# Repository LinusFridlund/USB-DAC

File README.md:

# USB-DAC
A high quality USB audio DAC.
This project is intended as a test for my larger music streamer project that implements a DAC chip together with a STM32 microconroller.
It accepts a music stream over USB, outputs the analog audio over balanced XLR connections and has an OLED display to show stream info. 

Image of a render of the PCBs together with  the case.

## Hardware
The main part of the hardware is the custom developed PCB housing the STM32, DAC chip and its accompanying components

### Microcontroller
A STM32H7 series microcontroller was chosen for its high performance and support for interfaces such as USB HS and SAI (Serial Audio Interface) which are used in the project. In addition I also have previous experience with STM32 based systems. Cost and power consumption were no priorities here since I am only building one unit and it is powered by an external power supply.

### DAC Chip
The DAC chip used is the ESS ES9039Q2M. It is a chip that is widely used in many other DACs meaning other designs are easy to reference. The datasheet includes important info about recommended output stages, power supply schemes and all the neccesary software details. For these reasons, along with its availability online made it a good choice.

### Power supply
A small PSU board with a Mean Well 12V supply feeds into a +-12V switching power supply on the main DAC board. The outptus then get filtered through a ferrite bead and a pi filter before being regulated to +-9V and 3.3V for the analog section. The incoming 12V also gets regulated down with less filtering to 5 and 3.3V for the digital components.

### PCB Design considerations
Extra attention had to be given to a couple of key areas in the PCB design in order to achieve a good result.
#### Stackup
A 4 layer stackup is used with the top and bottom being signal layers and the inner layers being ground and power in order to provide easy routing and better signal integrity.
#### Digital signal integrity
The USB signals and the ULPI signals between the USB PHY and the STM32 both operate at high frequencies and thus require proper impedance and length matching to ensure their functionality. 
#### 

## Software

The software development will start when the hardware is finished and ordered. So far I have only played around a bit and gotten a rough idea of how it will be structured.

## Current status
Currently the hardware design is finished and the PCBs have arrived. Currently the boards are being assembled, then the software development begins!

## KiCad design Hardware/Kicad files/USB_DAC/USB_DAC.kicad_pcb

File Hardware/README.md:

# Hardware

## PCB

## Enclosure

## Other parts

### Display
The display used is a 2.42 inch 128 x 64 px oled display from waveshare.
Link: https://www.waveshare.com/2.42inch-oled-module.htm

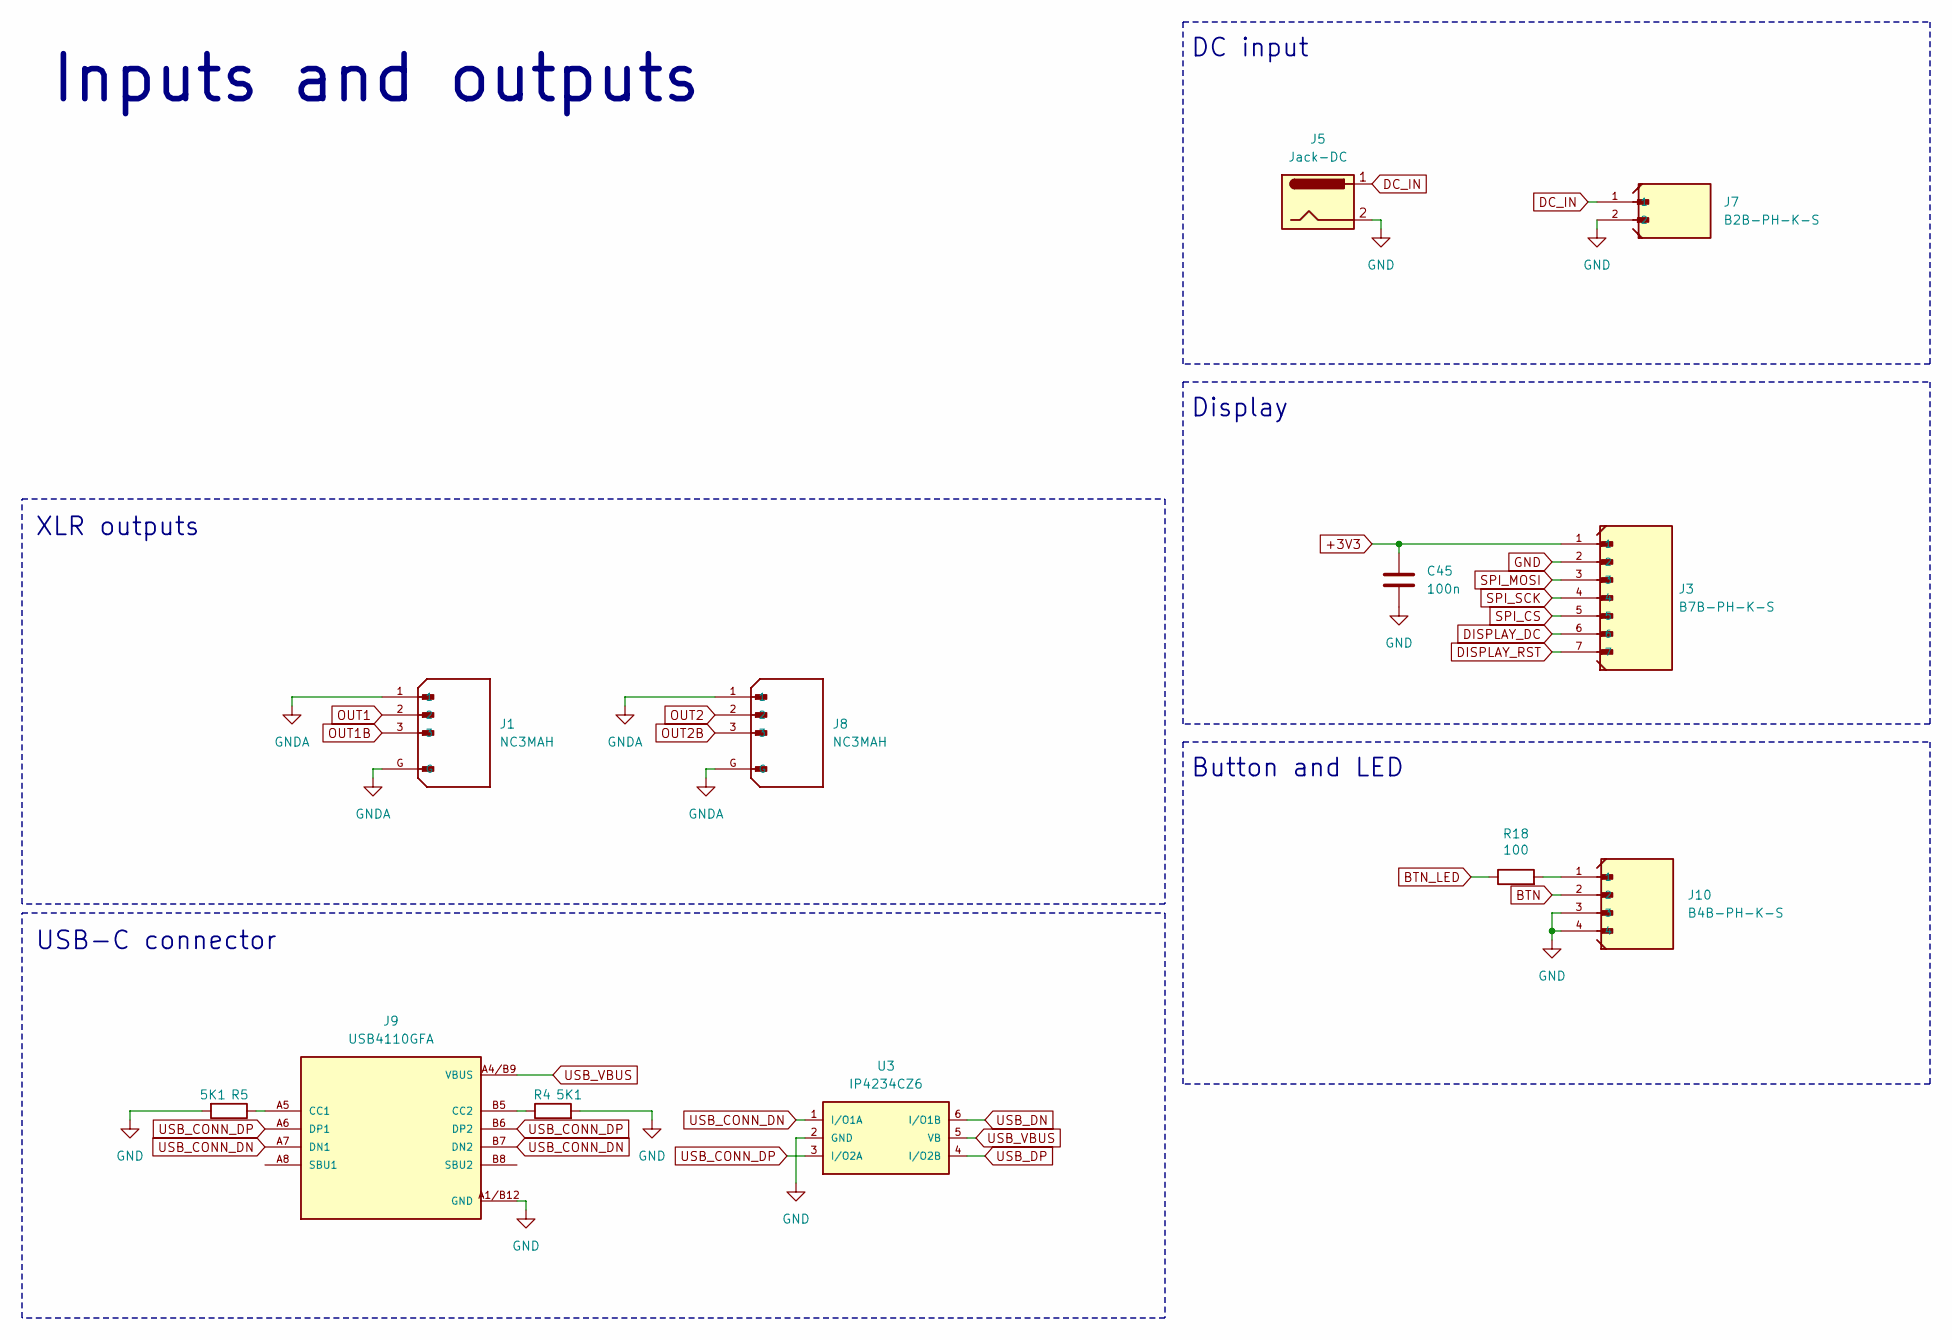
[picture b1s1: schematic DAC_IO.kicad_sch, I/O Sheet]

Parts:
C45: 100n; C_0603_1608Metric
J1, J8: NC3MAH; NEUTRIK_NC3MAH; PARTREV 30.03.09
J3: B7B-PH-K-S; JST_PH_B7B-PH-K_1x07_P2.00mm_Vertical
J5: Jack-DC; BarrelJack_Horizontal
J7: B2B-PH-K-S; JST_B2B-PH-K-S
J9: USB4110GFA; GCT_USB4110GFA
J10: B4B-PH-K-S; JST_B4B-PH-K-S
R4, R5: 5K1; R_0603_1608Metric
R18: 100; R_0603_1608Metric
U3: IP4234CZ6; SOT-457

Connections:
+3V3: C45.1, J3.1; also elsewhere on the board
BTN: J10.2; also elsewhere on the board
BTN_LED: R18.1; also elsewhere on the board
DC_IN: J5.1, J7.1; also elsewhere on the board
DISPLAY_DC: J3.6; also elsewhere on the board
DISPLAY_RST: J3.7; also elsewhere on the board
GNDA: J1.1, J1.G, J8.1, J8.G; also elsewhere on the board
unnamed: J9.A5 (CC1), R5.1
unnamed: J9.B5 (CC2), R4.1
unnamed: J10.1, R18.2
OUT1: J1.2; also elsewhere on the board
OUT1B: J1.3; also elsewhere on the board
OUT2: J8.2; also elsewhere on the board
OUT2B: J8.3; also elsewhere on the board
SPI_CS: J3.5; also elsewhere on the board
SPI_MOSI: J3.3; also elsewhere on the board
SPI_SCK: J3.4; also elsewhere on the board
USB_CONN_DN: J9.A7 (DN1), J9.B7 (DN2), U3.1 (I/O1A)
USB_CONN_DP: J9.A6 (DP1), J9.B6 (DP2), U3.3 (I/O2A)
USB_DN: U3.6 (I/O1B); also elsewhere on the board
USB_DP: U3.4 (I/O2B); also elsewhere on the board
USB_VBUS: J9.A4/B9 (VBUS), J9.B4/A9 (VBUS), U3.5 (VB); also elsewhere on the board

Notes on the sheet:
Button and LED
XLR outputs
Inputs and outputs
Display
DC input
USB-C connector

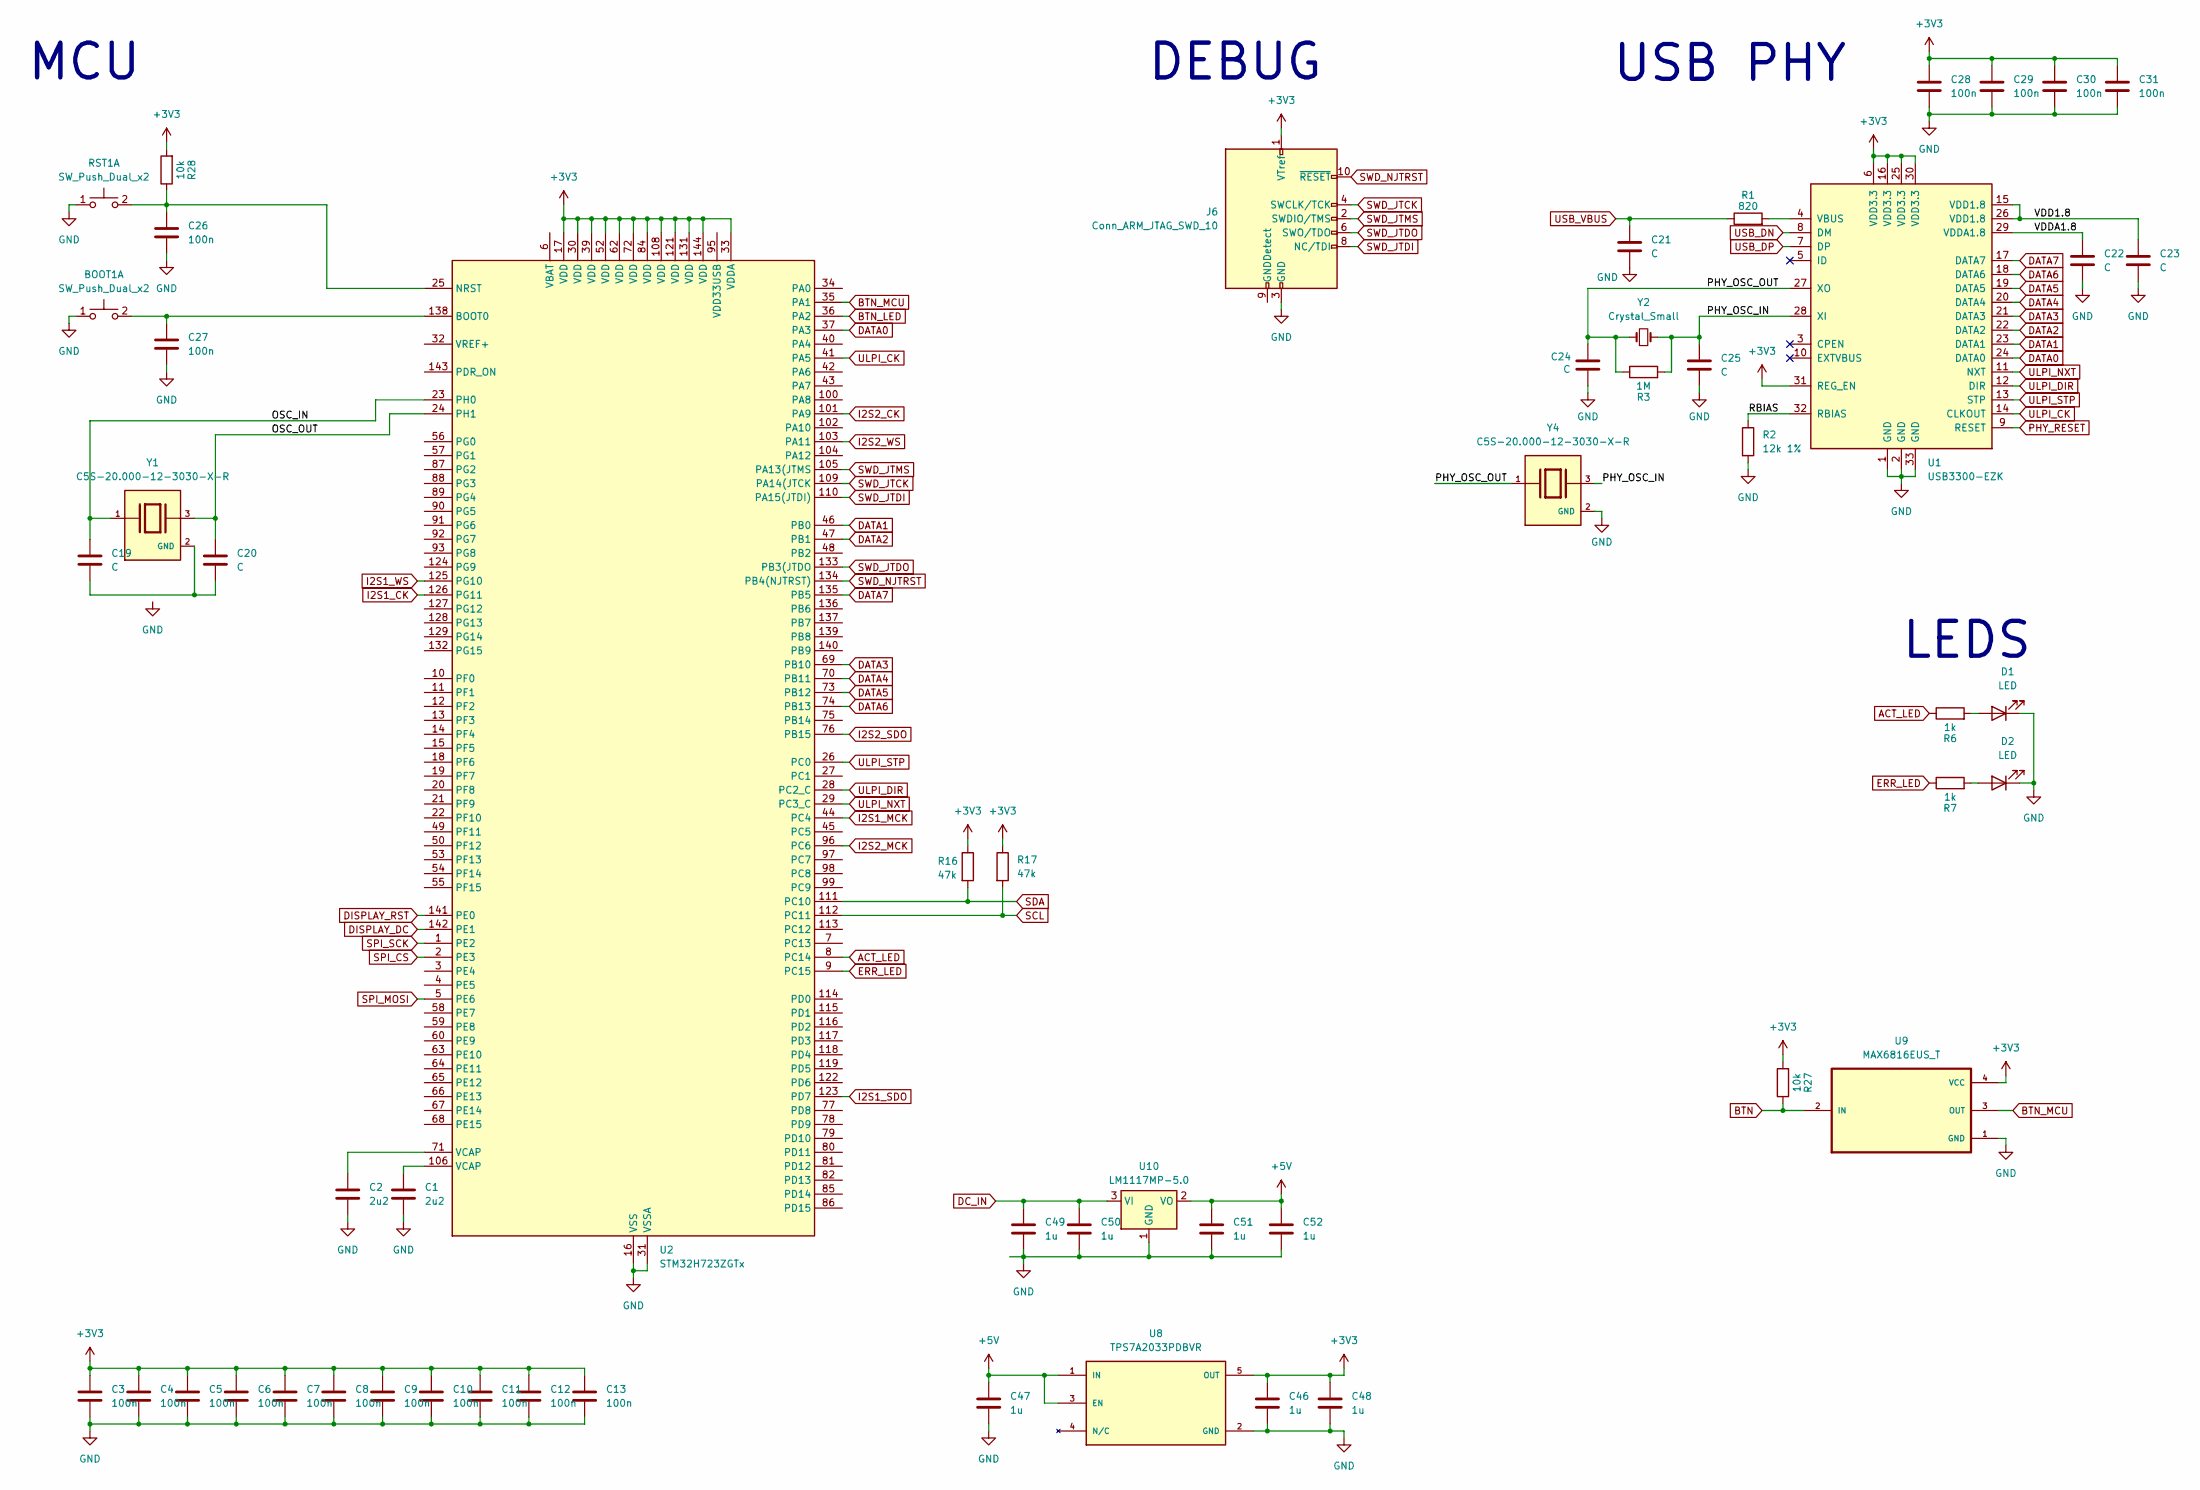
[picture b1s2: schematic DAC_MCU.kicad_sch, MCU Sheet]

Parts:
BOOT1: SW_Push_Dual_x2
C1, C2: 2u2; C_0603_1608Metric
C3, C4, C5, C6, C7, C8, C9, C10, C11, C12, C13, C26, C27, C28, C29, C30, C31: 100n; C_0603_1608Metric
C19, C20, C21, C22, C23, C24, C25: C; C_0603_1608Metric
C46, C47, C48, C49, C50, C51, C52: 1u; C_0603_1608Metric
D1, D2: LED; LED_0603_1608Metric
J6: Conn_ARM_JTAG_SWD_10; 2X10_BOXHEADER
R1: 820; R_0603_1608Metric
R2: 12k 1%; R_0603_1608Metric
R3: 1M; R_0603_1608Metric
R6, R7: 1k; R_0603_1608Metric
R16, R17: 47k; R_0603_1608Metric
R27, R28: 10k; R_0603_1608Metric
RST1: SW_Push_Dual_x2
U1: USB3300-EZK; QFN-32-1EP_5x5mm_P0.5mm_EP3.45x3.45mm
U2: STM32H723ZGTx; LQFP-144_20x20mm_P0.5mm
U8: TPS7A2033PDBVR; SOT95P280X145-5N; PARTREV H
U9: MAX6816EUS_T; SOT192P237X122-4N
U10: LM1117MP-5.0; SOT-223-3_TabPin2
Y1, Y4: C5S-20.000-12-3030-X-R; XTAL_C5S-20.000-12-3030-X-R; PARTREV N/A
Y2: Crystal_Small

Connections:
+3V3: C3.1, C4.1, C5.1, C6.1, C7.1, C8.1, C9.1, C10.1, C11.1, C12.1, C13.1, C28.1, C29.1, C30.1, C31.1, C46.1, C48.1, J6.1 (VTref), R16.1, R17.1, R27.2, R28.2, U1.6 (VDD3.3), U1.16 (VDD3.3), U1.25 (VDD3.3), U1.30 (VDD3.3), U1.31 (REG_EN), U2.17 (VDD), U2.30 (VDD), U2.33 (VDDA), U2.39 (VDD), U2.52 (VDD), U2.62 (VDD), U2.72 (VDD), U2.84 (VDD), U2.108 (VDD), U2.121 (VDD), U2.131 (VDD), U2.144 (VDD), U8.5 (OUT), U9.4 (VCC); also elsewhere on the board
+5V: C47.1, C51.1, C52.1, U8.1 (IN), U8.3 (EN), U10.2 (VO)
/MCU/OSC_IN: C19.1, U2.23 (PH0), Y1.1
/MCU/OSC_OUT: C20.1, U2.24 (PH1), Y1.3
/MCU/PHY_OSC_IN: C25.1, R3.2, U1.28 (XI), Y2.2, Y4.3
/MCU/PHY_OSC_OUT: C24.1, R3.1, U1.27 (XO), Y2.1, Y4.1
/MCU/RBIAS: R2.1, U1.32 (RBIAS)
/MCU/VDD1.8: C23.1, U1.15 (VDD1.8), U1.26 (VDD1.8)
/MCU/VDDA1.8: C22.1, U1.29 (VDDA1.8)
ACT_LED: R6.1, U2.8 (PC14)
BTN: R27.1, U9.2 (IN); also elsewhere on the board
BTN_LED: U2.36 (PA2); also elsewhere on the board
BTN_MCU: U2.35 (PA1), U9.3 (OUT)
DATA0: U1.24 (DATA0), U2.37 (PA3)
DATA1: U1.23 (DATA1), U2.46 (PB0)
DATA2: U1.22 (DATA2), U2.47 (PB1)
DATA3: U1.21 (DATA3), U2.69 (PB10)
DATA4: U1.20 (DATA4), U2.70 (PB11)
DATA5: U1.19 (DATA5), U2.73 (PB12)
DATA6: U1.18 (DATA6), U2.74 (PB13)
DATA7: U1.17 (DATA7), U2.135 (PB5)
DC_IN: C49.1, C50.1, U10.3 (VI); also elsewhere on the board
DISPLAY_DC: U2.142 (PE1); also elsewhere on the board
DISPLAY_RST: U2.141 (PE0); also elsewhere on the board
ERR_LED: R7.1, U2.9 (PC15)
I2S1_CK: U2.126 (PG11)
I2S1_MCK: U2.44 (PC4)
I2S1_SDO: U2.123 (PD7)
I2S1_WS: U2.125 (PG10)
I2S2_CK: U2.101 (PA9); also elsewhere on the board
I2S2_MCK: U2.96 (PC6)
I2S2_SDO: U2.76 (PB15); also elsewhere on the board
I2S2_WS: U2.103 (PA11); also elsewhere on the board
unnamed 44: BOOT1.2 (D), C27.1, U2.138 (BOOT0); also elsewhere on the board
unnamed: C1.1, U2.106 (VCAP)
unnamed: C2.1, U2.71 (VCAP)
unnamed: D1.2 (A), R6.2
unnamed: D2.2 (A), R7.2
unnamed 59: C26.1, R28.1, RST1.2 (D), U2.25 (NRST); also elsewhere on the board
unnamed: R1.2, U1.4 (VBUS)
PHY_RESET: U1.9 (RESET)
SCL: R17.2, U2.112 (PC11); also elsewhere on the board
SDA: R16.2, U2.111 (PC10); also elsewhere on the board
SPI_CS: U2.2 (PE3); also elsewhere on the board
SPI_MOSI: U2.5 (PE6); also elsewhere on the board
SPI_SCK: U2.1 (PE2); also elsewhere on the board
SWD_JTCK: J6.4 (SWCLK/TCK), U2.109 (PA14(JTCK)
SWD_JTDI: J6.8 (NC/TDI), U2.110 (PA15(JTDI))
SWD_JTDO: J6.6 (SWO/TDO), U2.133 (PB3(JTDO)
SWD_JTMS: J6.2 (SWDIO/TMS), U2.105 (PA13(JTMS)
SWD_NJTRST: J6.10 (~RESET), U2.134 (PB4(NJTRST))
ULPI_CK: U1.14 (CLKOUT), U2.41 (PA5)
ULPI_DIR: U1.12 (DIR), U2.28 (PC2_C)
ULPI_NXT: U1.11 (NXT), U2.29 (PC3_C)
ULPI_STP: U1.13 (STP), U2.26 (PC0)
USB_DN: U1.8 (DM); also elsewhere on the board
USB_DP: U1.7 (DP); also elsewhere on the board
USB_VBUS: C21.1, R1.1; also elsewhere on the board

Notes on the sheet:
LEDS
USB PHY
MCU
DEBUG

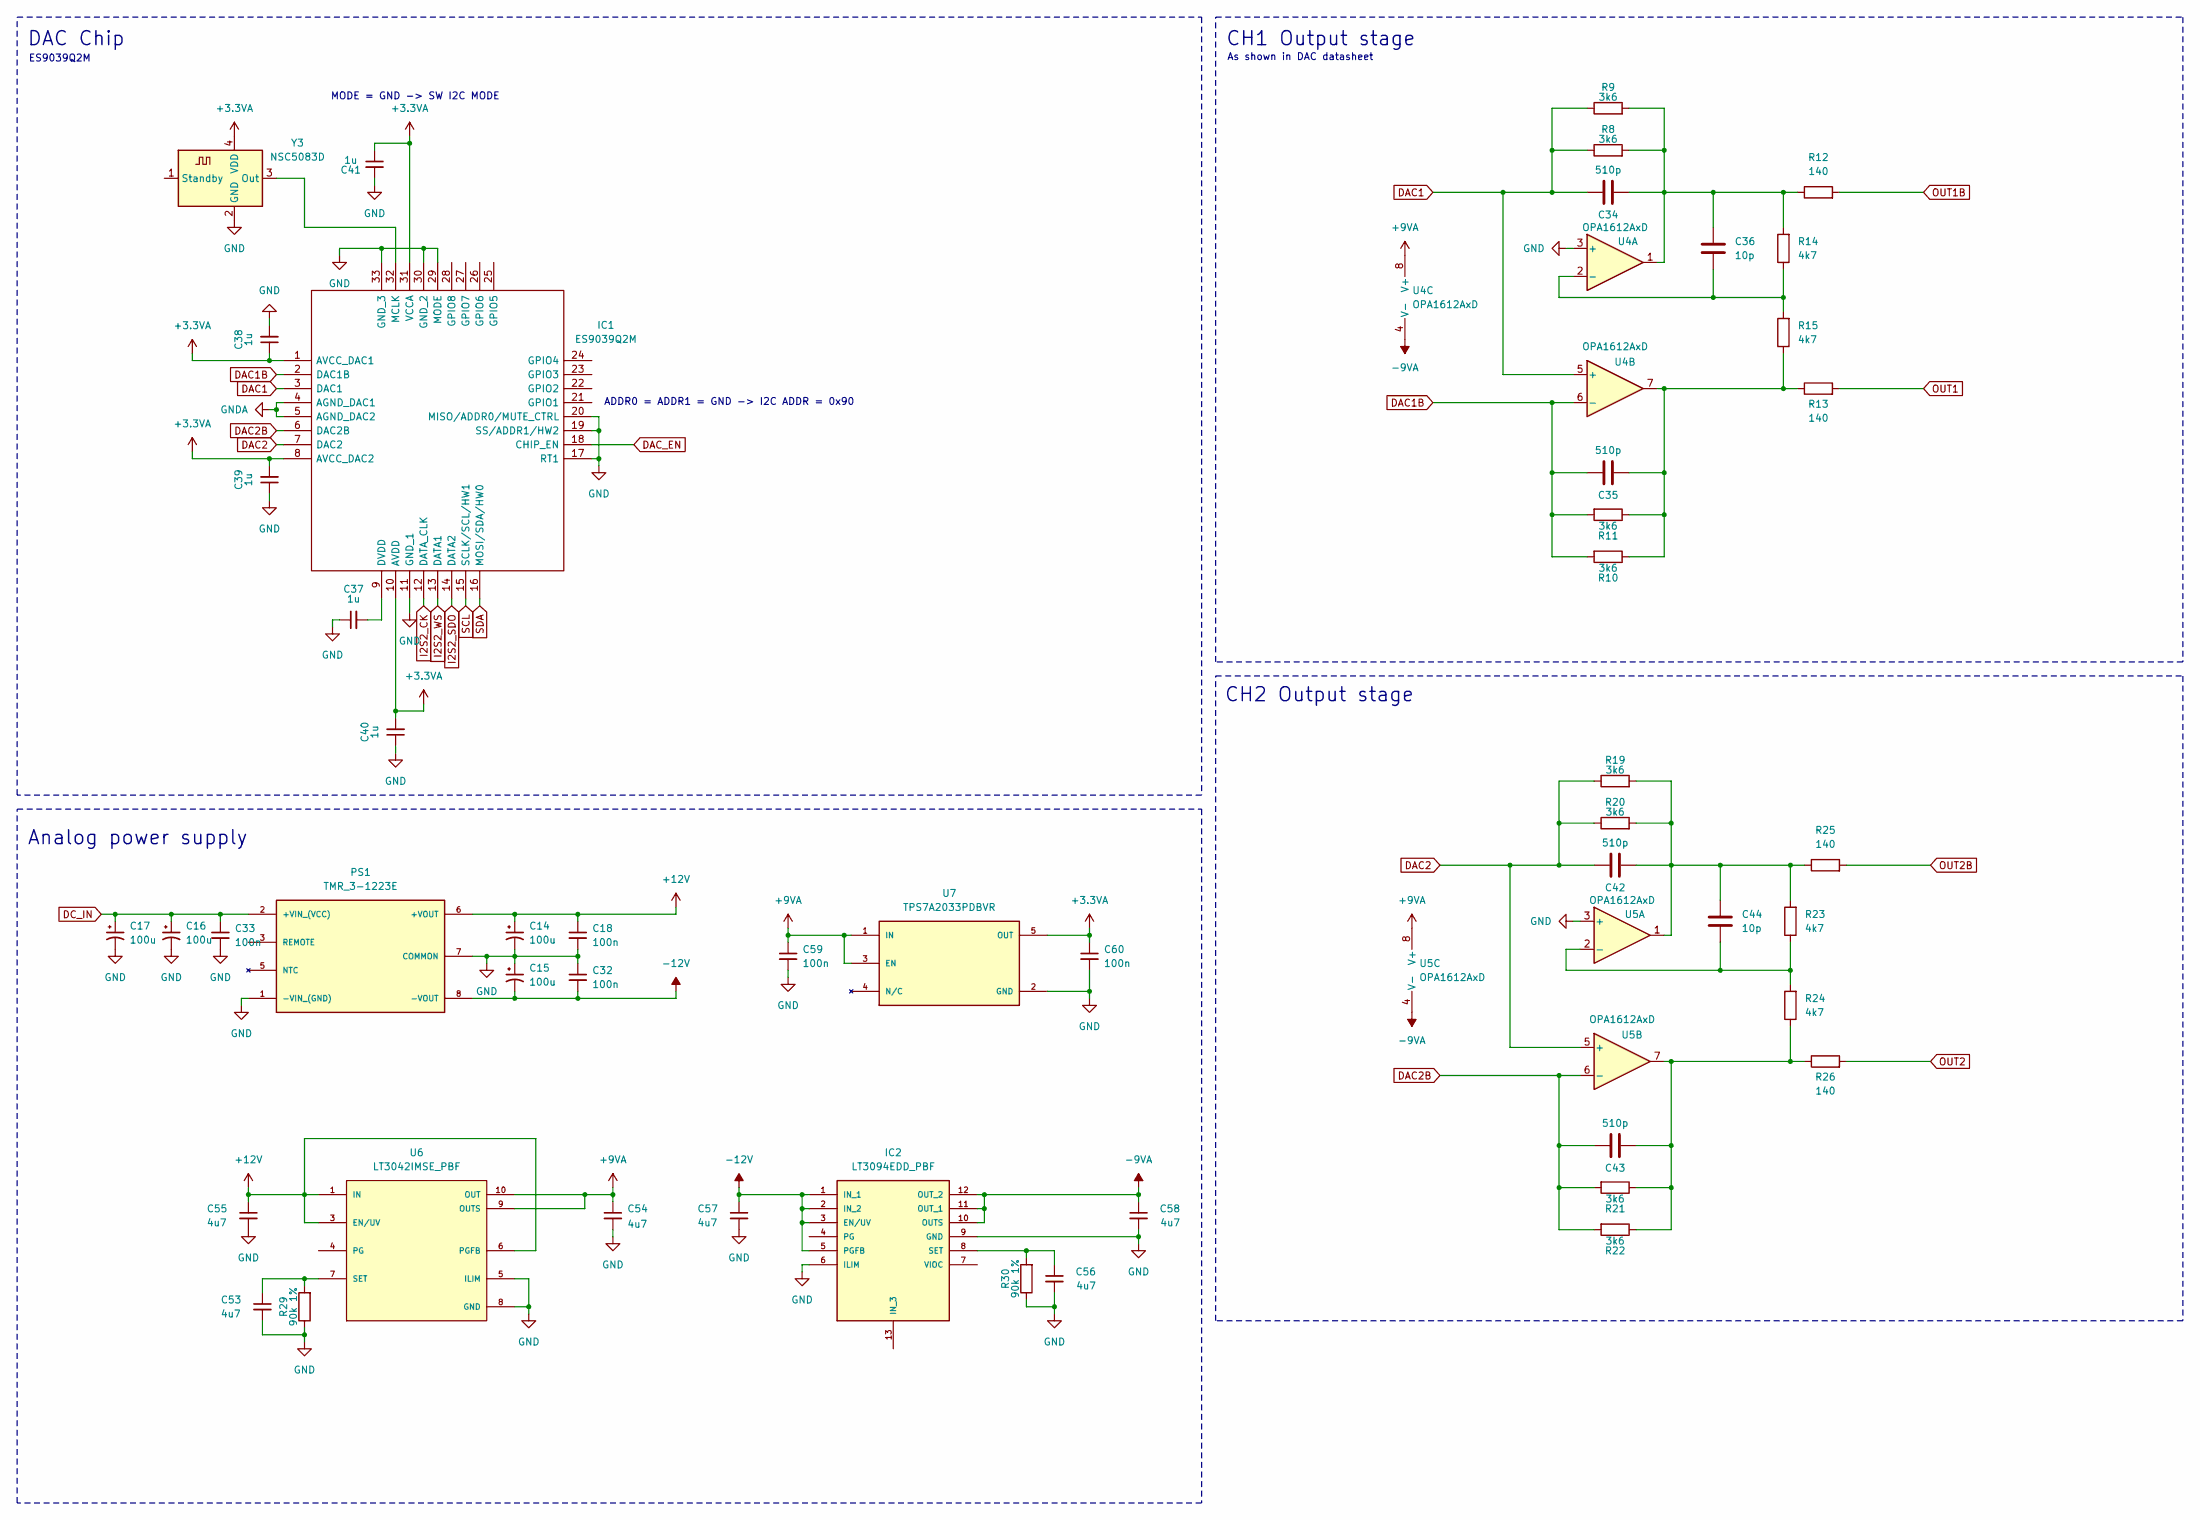
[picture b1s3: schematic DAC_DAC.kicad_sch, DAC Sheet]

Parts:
C14, C15, C16, C17: 100u; CP_Elec_4x4.5
C18, C32, C33, C59, C60: 100n; C_0603_1608Metric
C34, C35, C42, C43: 510p; C_0603_1608Metric
C36, C44: 10p; C_0603_1608Metric
C37, C38, C39, C40, C41: 1u; C_0603_1608Metric
C53, C54, C55, C56, C57, C58: 4u7; C_1206_3216Metric
IC1: ES9039Q2M; QFN-32-1EP_7x7mm_P0.65mm_EP4.7x4.7mm; Mouser Part Number 460-ES9039Q2M
IC2: LT3094EDD_PBF; SOP65P490X110-13N; MOUSER_PART_NUMBER 584-LT3094EDD#PBF
PS1: TMR_3-1223E; CONV_TMR_3-1223E; PARTREV March 9, 2021
R8, R9, R10, R11, R19, R20, R21, R22: 3k6; R_0603_1608Metric
R12, R13, R25, R26: 140; R_0603_1608Metric
R14, R15, R23, R24: 4k7; R_0603_1608Metric
R29, R30: 90k 1%; R_0603_1608Metric
U4, U5: OPA1612AxD; SOIC-8_3.9x4.9mm_P1.27mm
U6: LT3042IMSE_PBF; SOP50P490X110-11N; PARTREV B
U7: TPS7A2033PDBVR; SOT95P280X145-5N; PARTREV H
Y3: NSC5083D; Oscillator_SMD_Abracon_ASDMB-4Pin_2.5x2.0mm

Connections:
+3.3VA: C38.1, C39.2, C40.2, C41.1, C60.1, IC1.1 (AVCC_DAC1), IC1.8 (AVCC_DAC2), IC1.10 (AVDD), IC1.31 (VCCA), U7.5 (OUT), Y3.4 (VDD)
+9VA: C54.1, C59.1, U4.8 (V+), U5.8 (V+), U6.9 (OUTS), U6.10 (OUT), U7.1 (IN), U7.3 (EN)
+12V: C14.1, C18.1, C55.1, PS1.6 (+VOUT), U6.1 (IN), U6.2 (IN), U6.3 (EN/UV), U6.6 (PGFB)
-9VA: C58.1, IC2.10 (OUTS), IC2.11 (OUT_1), IC2.12 (OUT_2), U4.4 (V-), U5.4 (V-)
-12V: C15.2, C32.2, C57.1, IC2.1 (IN_1), IC2.2 (IN_2), IC2.3 (EN/UV), IC2.5 (PGFB), PS1.8 (-VOUT)
DAC1: C34.1, IC1.3 (DAC1), R8.1, R9.1, U4.5 (+)
DAC1B: C35.1, IC1.2 (DAC1B), R10.2, R11.2, U4.6 (-)
DAC2: C42.1, IC1.7 (DAC2), R19.1, R20.1, U5.5 (+)
DAC2B: C43.1, IC1.6 (DAC2B), R21.2, R22.2, U5.6 (-)
DAC_EN: IC1.18 (CHIP_EN)
DC_IN: C16.1, C17.1, C33.1, PS1.2 (+VIN_(VCC)); also elsewhere on the board
GNDA: IC1.4 (AGND_DAC1), IC1.5 (AGND_DAC2); also elsewhere on the board
I2S2_CK: IC1.12 (DATA_CLK); also elsewhere on the board
I2S2_SDO: IC1.14 (DATA2); also elsewhere on the board
I2S2_WS: IC1.13 (DATA1); also elsewhere on the board
unnamed: C34.2, C36.1, R8.2, R9.2, R12.1, R14.2, U4.1
unnamed: C35.2, R10.1, R11.1, R13.1, R15.1, U4.7
unnamed: C42.2, C44.1, R19.2, R20.2, R23.2, R25.1, U5.1
unnamed: C43.2, R21.1, R22.1, R24.1, R26.1, U5.7
unnamed: C37.2, IC1.9 (DVDD)
unnamed: IC1.32 (MCLK), Y3.3 (Out)
unnamed: C56.1, IC2.8 (SET), R30.2
unnamed: C36.2, R14.1, R15.2, U4.2 (-)
unnamed: C44.2, R23.1, R24.2, U5.2 (-)
unnamed: C53.1, R29.2, U6.7 (SET)
OUT1: R13.2; also elsewhere on the board
OUT1B: R12.2; also elsewhere on the board
OUT2: R26.2; also elsewhere on the board
OUT2B: R25.2; also elsewhere on the board
SCL: IC1.15 (SCLK/SCL/HW1); also elsewhere on the board
SDA: IC1.16 (MOSI/SDA/HW0); also elsewhere on the board

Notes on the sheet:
ES9039Q2M
As shown in DAC datasheet
Analog power supply
CH1 Output stage
CH2 Output stage
DAC Chip
ADDR0 = ADDR1 = GND -> I2C ADDR = 0x90
MODE = GND -> SW I2C MODE

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
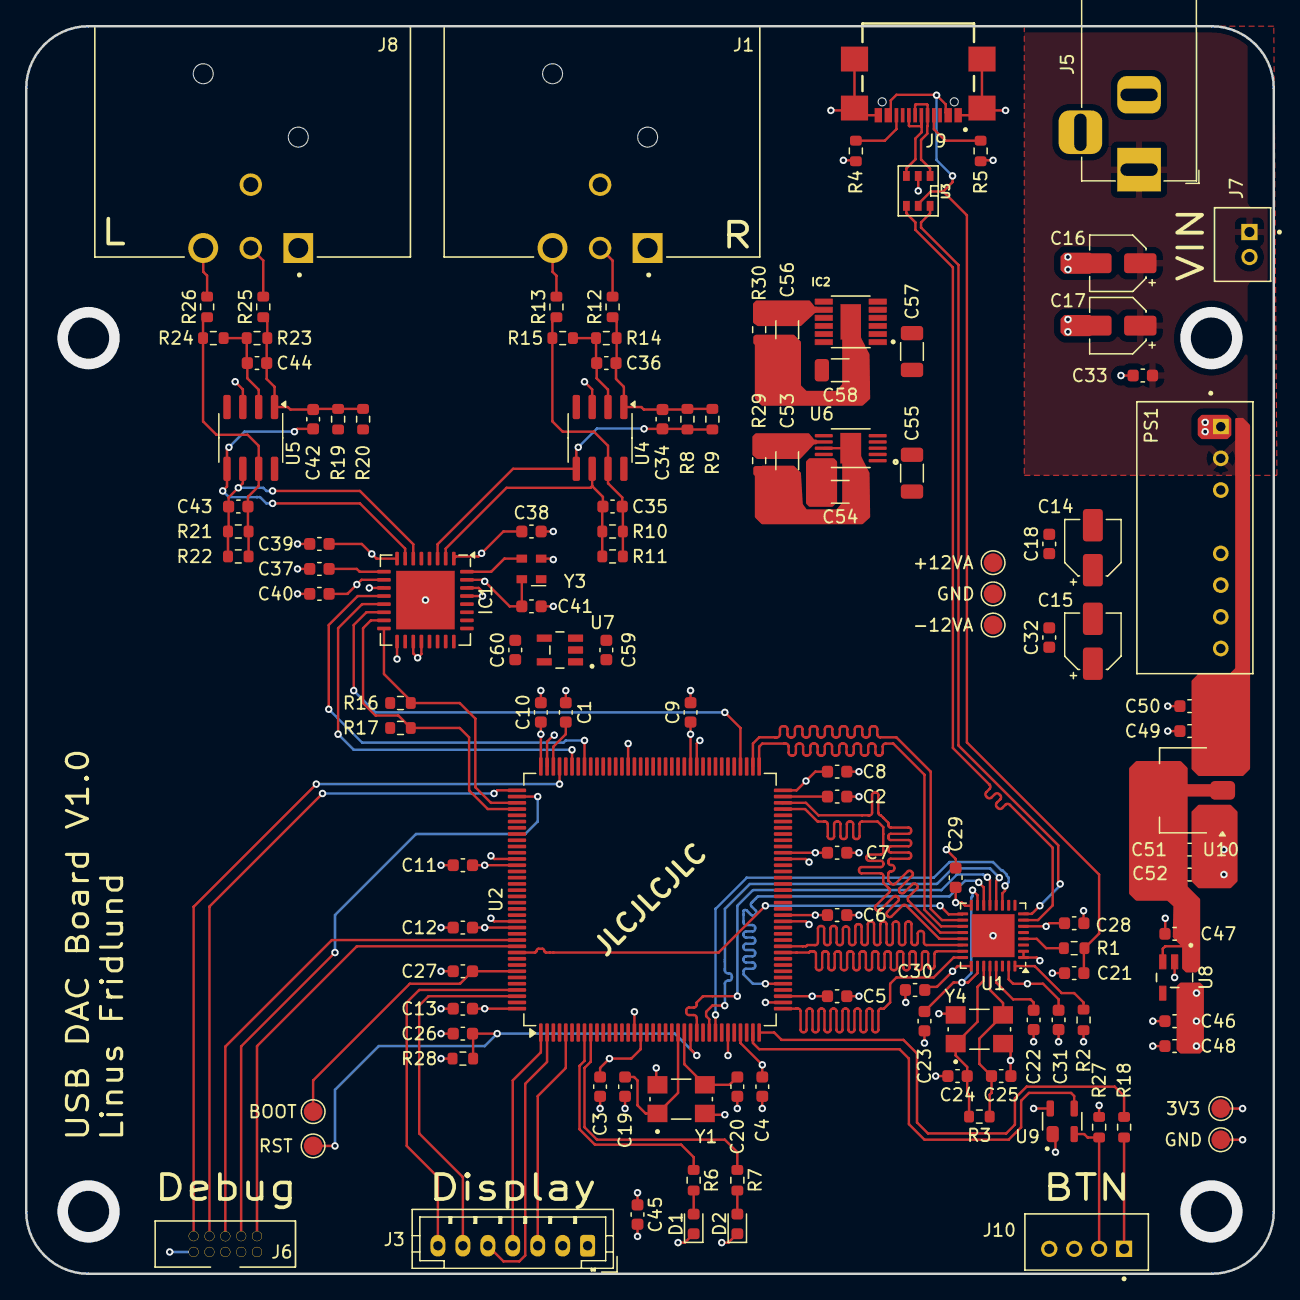
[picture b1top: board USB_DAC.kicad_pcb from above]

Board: 4 copper layers, 100.0 x 100.0 mm, 123 parts (0 on the bottom side), 82 nets.

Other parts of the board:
3V3: TestPoint_Pad_D1.5mm
+12VA: TestPoint_Pad_D1.5mm
-12VA: TestPoint_Pad_D1.5mm
BOOT: TestPoint_Pad_D1.5mm
GND: TestPoint_Pad_D1.5mm
GND#2: TestPoint_Pad_D1.5mm
RST: TestPoint_Pad_D1.5mm

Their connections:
+3V3: 3V3.1; also elsewhere on the board
unnamed 44: BOOT.1; also elsewhere on the board
unnamed 59: RST.1; also elsewhere on the board

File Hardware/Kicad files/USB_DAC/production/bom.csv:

Designator,Footprint,Quantity,Value,LCSC Part #
"C1, C2",0603,2,2u2,
"C10, C11, C12, C13, C18, C26, C27, C28, C29, C3, C30, C31, C32, C33, C4, C45, C5, C6, C7, C8, C9",0603,21,100n,
"C14, C15, C16, C17",CP_Elec_4x4.5,4,100u,
"C19, C20, C21, C22, C23, C24, C25",0603,7,C,
"C34, C35, C42, C43",0603,4,510p,
"C36, C44",0603,2,10p,
"C37, C38, C39, C40, C41",0603,5,1u,
"D1, D2",0603,2,LED,
IC1,QFN-32-1EP_7x7mm_P0.65mm_EP4.7x4.7mm,1,ES9039Q2M,
IC2,SOP65P490X110-13N,1,LT3094EDD_PBF,
"J1, J8",NEUTRIK_NC3MAH,2,NC3MAH,
J10,JST_B4B-PH-K-S,1,B4B-PH-K-S,
J2,RCJ-2221,1,RCJ-2234,
J3,JST_PH_B7B-PH-K_1x07_P2.00mm_Vertical,1,B7B-PH-K-S,
J5,BarrelJack_Horizontal,1,Jack-DC,
J6,2X10_BOXHEADER,1,Conn_ARM_JTAG_SWD_10,
J7,JST_B2B-PH-K-S,1,B2B-PH-K-S,
J9,GCT_USB4110GFA,1,USB4110GFA,
PS1,CONV_TMR_3-1223E,1,TMR_3-1223E,
R1,0603,1,820,
"R10, R11, R19, R20, R21, R22, R8, R9",0603,8,3k6,
"R12, R13, R25, R26",0603,4,140,
"R14, R15, R23, R24",0603,4,4k7,
"R16, R17",0603,2,47k,
R18,0603,1,100,
R2,0603,1,12k 1%,
R3,0603,1,1M,
"R4, R5",0603,2,5K1,
"R6, R7",0603,2,1k,
U1,QFN-32-1EP_5x5mm_P0.5mm_EP3.45x3.45mm,1,USB3300-EZK,
U2,LQFP-144_20x20mm_P0.5mm,1,STM32H723ZGTx,
U3,SOT-457,1,IP4234CZ6,
"U4, U5",SOIC-8_3.9x4.9mm_P1.27mm,2,OPA1612AxD,
U6,SOP50P490X110-11N,1,LT3042IMSE_PBF,
U7,SOT95P280X145-5N,1,TPS7A2033PDBVR,
Y3,Oscillator_SMD_Abracon_ASDMB-4Pin_2.5x2.0mm,1,NSC5083D,

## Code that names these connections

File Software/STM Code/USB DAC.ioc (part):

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Mcu.Name=STM32H723ZGTx
Mcu.Package=LQFP144
Mcu.UserName=STM32H723ZGTx
PA11.Mode=Half_Duplex_Master_Tx
PA11.Signal=I2S2_WS
PA3.Mode=Device_HS
PA3.Signal=USB_OTG_HS_ULPI_D0
PA5.Mode=Device_HS
PA5.Signal=USB_OTG_HS_ULPI_CK
PA9.Mode=Half_Duplex_Master_Tx
PA9.Signal=I2S2_CK
PB0.Mode=Device_HS
PB0.Signal=USB_OTG_HS_ULPI_D1
PB1.Mode=Device_HS
PB1.Signal=USB_OTG_HS_ULPI_D2
PB10.Mode=Device_HS
PB10.Signal=USB_OTG_HS_ULPI_D3
PB11.Mode=Device_HS
PB11.Signal=USB_OTG_HS_ULPI_D4
PB12.Mode=Device_HS
PB12.Signal=USB_OTG_HS_ULPI_D5
PB13.Mode=Device_HS
PB13.Signal=USB_OTG_HS_ULPI_D6
PB15.Mode=Half_Duplex_Master_Tx
PB15.Signal=I2S2_SDO
PB5.Mode=Device_HS
PB5.Signal=USB_OTG_HS_ULPI_D7
PC0.Mode=Device_HS
PC0.Signal=USB_OTG_HS_ULPI_STP
PC10.Mode=I2C
PC10.Signal=I2C5_SDA
PC11.Mode=I2C
PC11.Signal=I2C5_SCL
PC2_C.Mode=Device_HS
PC2_C.Signal=USB_OTG_HS_ULPI_DIR
PC3_C.Mode=Device_HS
PC3_C.Signal=USB_OTG_HS_ULPI_NXT
PE12.Mode=SAI_B_Master
PE12.Signal=SAI4_SCK_B
PE2.Mode=TX_Only_Simplex_Unidirect_Master
PE2.Signal=SPI4_SCK
PE6.Mode=TX_Only_Simplex_Unidirect_Master
PE6.Signal=SPI4_MOSI
PG10.Mode=SAI_B_Master
PG10.Signal=SAI4_SD_B
PG9.Mode=SAI_B_Master
PG9.Signal=SAI4_FS_B
PH0-OSC_IN.Mode=HSE-External-Oscillator
PH0-OSC_IN.Signal=RCC_OSC_IN
PH1-OSC_OUT.Mode=HSE-External-Oscillator
PH1-OSC_OUT.Signal=RCC_OSC_OUT
RCC.HSE_VALUE=24000000
RCC.SYSCLKFreq_VALUE=64000000
board=custom

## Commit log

2025-12-18 Rename USB DAC v8.png to USBDACrender.png
2025-12-20 Added Kicad files
2025-12-20 added gitignore
2025-12-20 added more readme files
2025-12-22 added STM code files and modified PCB
2025-12-28 Add PCB image
2025-12-30 Updated PCB and schematics
2026-02-27 Rename USBDACrender.PNG to USBDACrender.png
